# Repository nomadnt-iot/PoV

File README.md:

- [What is a PoV display](#what-is-a-pov-display)
- [Introduction](#introduction)
- [How it's work](#how-its-work)
  - [Output pins](#output-pins)
  - [Display text](#display-text)
- [Hardware](#hardware)
  - [Components used](#components-used)
- [Useful links](#useful-links)
- [TODO](#todo)

# What is a PoV display

[Here](https://en.wikipedia.org/wiki/Persistence_of_vision) the definition of Persistence of Vision Display from wikipedia.

*The term "persistence of vision display" or "POV display" has been used for LED display devices that compose images by displaying one spatial portion at a time in rapid succession, (for example, one column of pixels every few milliseconds). A two-dimensional POV display is often accomplished by means of rapidly moving a single row of LEDs along a linear or circular path. The effect is that the image is perceived as a whole by the viewer as long as the entire path is completed during the visual persistence time of the human eye. A further effect is often to give the illusion of the image floating in mid-air.*

A common example of this can be seen in the use of bicycle wheel lights that produce patterns.

# Introduction

**PoV** is a very simple **P**ersistent **o**f **V**ision display based on Atmel ATTinyX5 chips family.
It is making use of all 5 pins available on ATTinyX5 chips family and it is written in pure AVR-C.

# How it's work

The ATTinyX5 has only 5 GPIO pins suitable to drive our display. The [Schematic](hardware/schematic.pdf) will help you to better understand how leds are connected to each pin.

It is using only 16 bytes of RAM and 634 bytes of Flash memory

```sh
RAM:   [          ]   3.1% (used 16 bytes from 512 bytes)
Flash: [=         ]   7.7% (used 634 bytes from 8192 bytes)
```

## Output pins

First we have to set all the 5 pins on the ATTinyX5 as output.

```c
#include <pov.h>

int main(void)
{
    DDRB = 0x1F; // 0x1F is equals to 31 that is equals to 1 << 5
    ...
}
```

## Display text

In order to display text we need to call the `display` method in a loop like the following

```c
#include <pov.h>

int main(void)
{
    DDRB = 0x1F; // 0x1F is equals to 31 that is equals to 1 << 5

    while (1)
    {
        display("jacopo sallemi", 2, 5);
    }
}
```

Than the `display` function is looping through all the chars in the string and call the `display_char` method that is just getting the encoded corrisponding `value` related to the processed char and than configure the `PORTB` in accoding to the value.

```c
void display_char(const char c, unsigned char delayTime, unsigned char charBreak)
{
    for (unsigned char i = 0; i < (sizeof(symbols) / sizeof(struct symbol_t)); i++)
    {
        if (c == pgm_read_byte(&symbols[i].code))
        {
            for (unsigned char j = 0; j < COLS_COUNT; j++)
            {
                // Configure PORTB with the current encoded value
                PORTB = pgm_read_byte(&symbols[i].value[j]);
                _delay_ms(delayTime);
            }

            // Turn off all the output
            PORTB = 0;
        }
    }

    _delay_ms(charBreak);
}
```

# Hardware 

The [Hardware](hardware) folder contains my first eagle implementation and a new version based on KiKad.
Anyways you can use both of them as starting point to your PoV project. 

- [Schematic](hardware/schematic.pdf)
- [3D model](hardware/PoV.png)

## Components used

- 1x ATTinyX5
- 5x leds green
- 1x 100 nF decoupling capacitor
- 1x switch
- 1x R2032
- 1x battery holder for CR2032
- Stripboard
- Some soldering cable

The circuit is power by a CR2032 so this is the reason for the switch... to turn on and off the PoV as required.  
The decoupling capacitor is always a good idea to have expecially when we are powering devices through battery and is connected as closet as possible the ATTinyX5.  
And finally The leds are all connected from the bottom to the top to the ATTinyX5's pins PB0, PB1, PB2, PB3, PB4.

```
LEDS CONNECTION

            PB4 [] LED5

            PB3 [] LED4

            PB2 [] LED3

            PB1 [] LED2

            PB0 [] LED1

              +-\/-+
        PB5  1|    |8   VCC
(LED4)  PB3  2|    |7   PB2  (LED3)
(LED5)  PB4  3|    |6   PB1  (LED2)
        GND  4|    |5   PB0  (LED1)
              +----+

```

The ATTinyX5 has only `PORTB` and can handle only 5 GPIO so [symbols.h](include/symbols.h) is provided to handle only char 5x5 pixels.  
Feel free to change it in according to your requirements.

# Useful links

- [Programming AVR Microcontrollers in C - O'Reilly Webcast](https://youtu.be/ERY7d7W-6nA)
- [Font 5x5 pixel resource 1](https://www.dafont.com/5x5.font)
- [Font 5x5 pixel resource 2](https://www.1001fonts.com/5x5-font.html)
- [ATTinyX5 Datasheet](https://ww1.microchip.com/downloads/en/DeviceDoc/Atmel-2586-AVR-8-bit-Microcontroller-ATtiny25-ATtiny45-ATtiny85_Datasheet.pdf)

# TODO

- make code non blocking
- add V-USB support for micronucleous firmare.
- reorganize fonts

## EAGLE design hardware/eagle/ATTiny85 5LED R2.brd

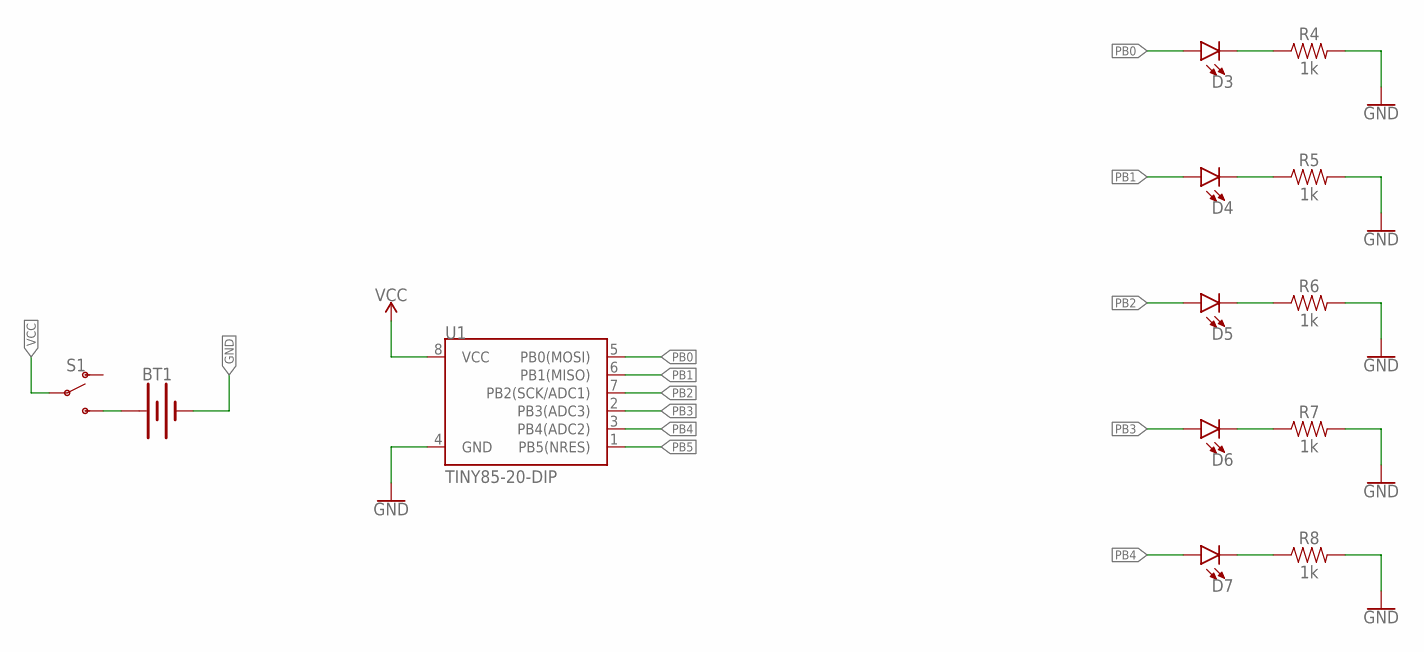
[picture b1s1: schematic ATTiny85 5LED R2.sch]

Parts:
BT1: BATTERY-12MM_PTH; BATTCON_12MM_PTH
D3, D4, D5, D6, D7: LED5MM; LED_5MM
R4, R5, R6, R7, R8: 1k; AXIAL-0.3
S1: SWITCH-SPDT-PTH-11.6X4.0MM-KIT; SWITCH_SPDT_PTH_11.6X4.0MM_KIT
U1: TINY85-20-DIP; DIP08_MCU

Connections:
GND: BT1.GND (-), R4.P$2 (2), R5.P$2 (2), R6.P$2 (2), R7.P$2 (2), R8.P$2 (2), U1.4 (GND)
unnamed: BT1.VCC@1 (+), S1.3 (S)
unnamed: D3.K (C), R4.P$1 (1)
unnamed: D4.K (C), R5.P$1 (1)
unnamed: D5.K (C), R6.P$1 (1)
unnamed: D6.K (C), R7.P$1 (1)
unnamed: D7.K (C), R8.P$1 (1)
PB0: D3.A, U1.5 (PB0(MOSI))
PB1: D4.A, U1.6 (PB1(MISO))
PB2: D5.A, U1.7 (PB2(SCK/ADC1))
PB3: D6.A, U1.2 (PB3(ADC3))
PB4: D7.A, U1.3 (PB4(ADC2))
PB5: U1.1 (PB5(NRES))
VCC: S1.2, U1.8 (VCC)

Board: 2 copper layers, 13 parts (0 on the bottom side), 13 nets, no tracks yet.

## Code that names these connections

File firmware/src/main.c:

/**
 *  PoV is a very simple persistent of vision display that use ATTiny85 and 5 leds
 */
#include <util/delay.h>
#include <hardware.h>
#include <uPoV.h>

// defining led array
unsigned char LED[LEDS_COUNT] = {PB4, PB3, PB2, PB1, PB0};

int main(void)
{
    // Heremany ways how to assign pin a outout 
    // LEDS_DDR |= (_BV(PB0) | _BV(PB1) | _BV(PB2) | _BV(PB3) | _BV(PB4));
    // LEDS_DDR = 0x1F;
    // LEDS_DDR = 32;
    // LEDS_DDR = (1 << LEDS_COUNT) - 1;

    for (unsigned char i = 0; i < LEDS_COUNT; i++)
    {
        _sbi(LEDS_PORT, LED[i]);
        _delay_ms(250);
    }

    for (unsigned char i = LEDS_COUNT; i > 0; i--)
    {
        _cbi(LEDS_PORT, LED[i - 1]);
        _delay_ms(250);
    }

    while (1)
    {
        display(LED, "jacopo sallemi", 2, 5);
    }
}

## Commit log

2017-10-22 initial import
2017-10-22 removed digispark from patrformio and optimize memory usage using uint8_t instead of int
2017-10-22 added alphabet header file for code organizing
2017-10-22 moved everithing to library uPoV
2017-10-22 massive use of progmem for alphabet and gain more more space
2017-11-01 added digispark-tiny support
2018-02-25 remove unused code and init support for trinket
2018-09-23 reorganizing project directory
2018-10-21 improving code organization and documentation
2018-10-22 added bitwise operation to turn on and off the leds line
2018-10-24 init to work on new symbols
2019-05-25 updating eagle files
2019-05-26 updating symbols table
2019-05-26 fixed fonts
2021-09-25 move uPoV as a library
2021-09-25 improved readme
2021-09-26 working on initial version avr-c
2021-09-26 make pov working with avr-c
2021-09-26 removed wrong led array
2021-09-26 sync
2021-09-26 last stable
2021-09-26 shrink the code as much as possible
2021-09-26 reorganizing layout
2021-09-26 improve readme
2021-09-27 improving doc
2021-09-27 move eagle files inside eagle folder
2021-09-27 added kicad schematic
2021-09-27 updated kicad schematic
2021-09-27 woking on kicad
2021-09-27 improved kicad project
2021-09-27 added first schematic draw
2021-09-27 removed todo section
2021-09-27 imrpving readme
2021-09-27 added table of contents
2021-10-01 added missed route on pcb
2021-10-01 improved design
2021-10-04 improve readme and optimize code
2021-10-10 now pov is programmable from board

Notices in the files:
parts and their libraries:
SparkFun-Batteries: Licensing: Creative Commons ShareAlike 4.0 International - https://creativecommons.org/licenses/by-sa/4.0
